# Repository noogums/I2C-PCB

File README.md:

i2c-sensor-logger:
  - A 2-layer PCB that logs temperature, humidity, and ambient light over I2C to CSV via USB serial and displays live readings on an SSD1306 OLED. 
    Built around the Raspberry Pi Pico W with TI HDC1080 and OPT3001 sensors.

Hardware:
  - Raspberry Pi Pico W
  - TI HDC1080 — temperature and humidity (±0.2°C, 14-bit)
  - TI OPT3001 — ambient light (23-bit dynamic range)
  - SSD1306 128x64 OLED display
  - MCP1700 3.3V LDO regulator
  - 2-layer FR4 PCB, manufactured by JLCPCB

Measurements: (updated once board comes in)
  - I2C bus waveforms — scope screenshot of SDA/SCL
  - Rise time measured vs calculated
  - Temperature accuracy vs reference thermometer
  - Power consumption on 3.3V rail
  - I2C frequency limit before communication fails

Schematic:

PCB:
  -Top:

  -Back:

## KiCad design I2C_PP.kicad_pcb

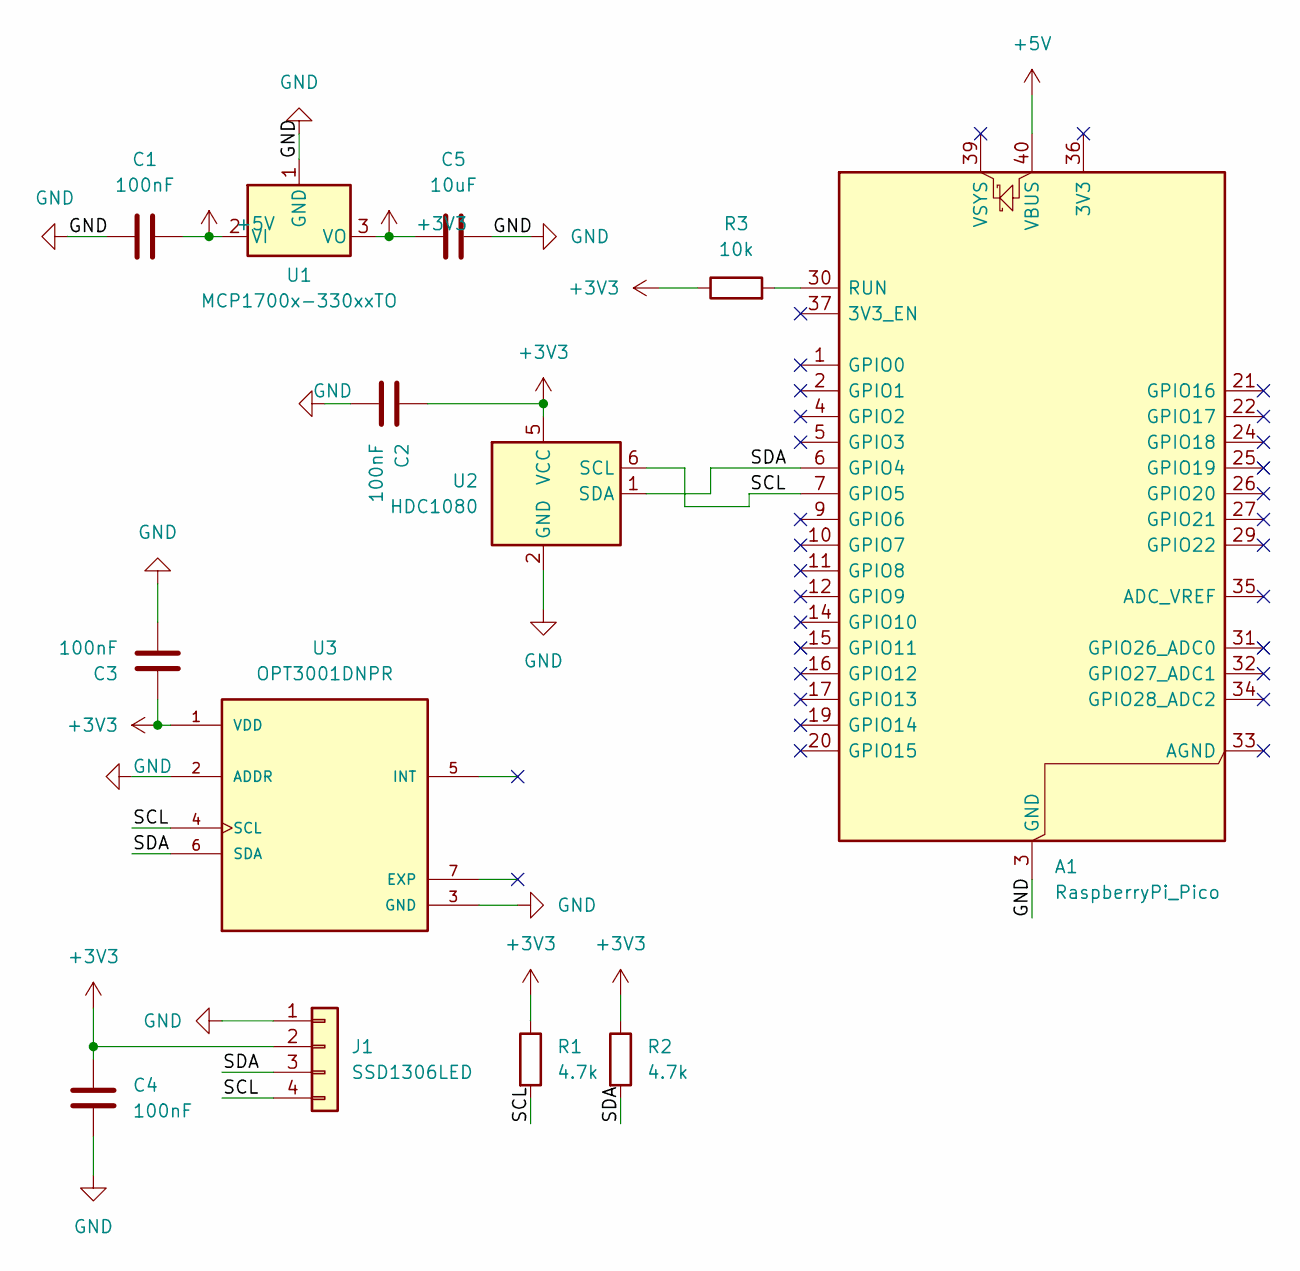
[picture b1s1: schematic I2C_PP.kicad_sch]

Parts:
A1: RaspberryPi_Pico; RaspberryPi_Pico_Common_Unspecified
C1, C2, C3, C4: 100nF; C_0603_1608Metric
C5: 10uF; C_0805_2012Metric
J1: SSD1306LED; PinHeader_1x04_P2.54mm_Vertical
R1, R2: 4.7k; R_0603_1608Metric
R3: 10k; R_0603_1608Metric
U1: MCP1700x-330xxTO; TO-92_Inline
U2: HDC1080; Texas_PWSON-N6
U3: OPT3001DNPR; SON65P200X200X65-7N

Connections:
+3V3: C2.1, C3.1, C4.1, C5.1, J1.2, R1.1, R2.1, R3.1, U1.3 (VO), U2.5 (VCC), U3.1 (VDD)
+5V: A1.40 (VBUS), C1.2, U1.2 (VI)
/SCL: A1.7 (GPIO5), J1.4, R1.2, U2.6 (SCL), U3.4 (SCL)
/SDA: A1.6 (GPIO4), J1.3, R2.2, U2.1 (SDA), U3.6 (SDA)
GND: A1.3 (GND), A1.8 (GND), A1.13 (GND), A1.18 (GND), A1.23 (GND), A1.28 (GND), A1.38 (GND), C1.1, C2.2, C3.2, C4.2, C5.2, J1.1, U1.1 (GND), U2.2 (GND), U3.2 (ADDR), U3.3 (GND)
unnamed: A1.30 (RUN), R3.2

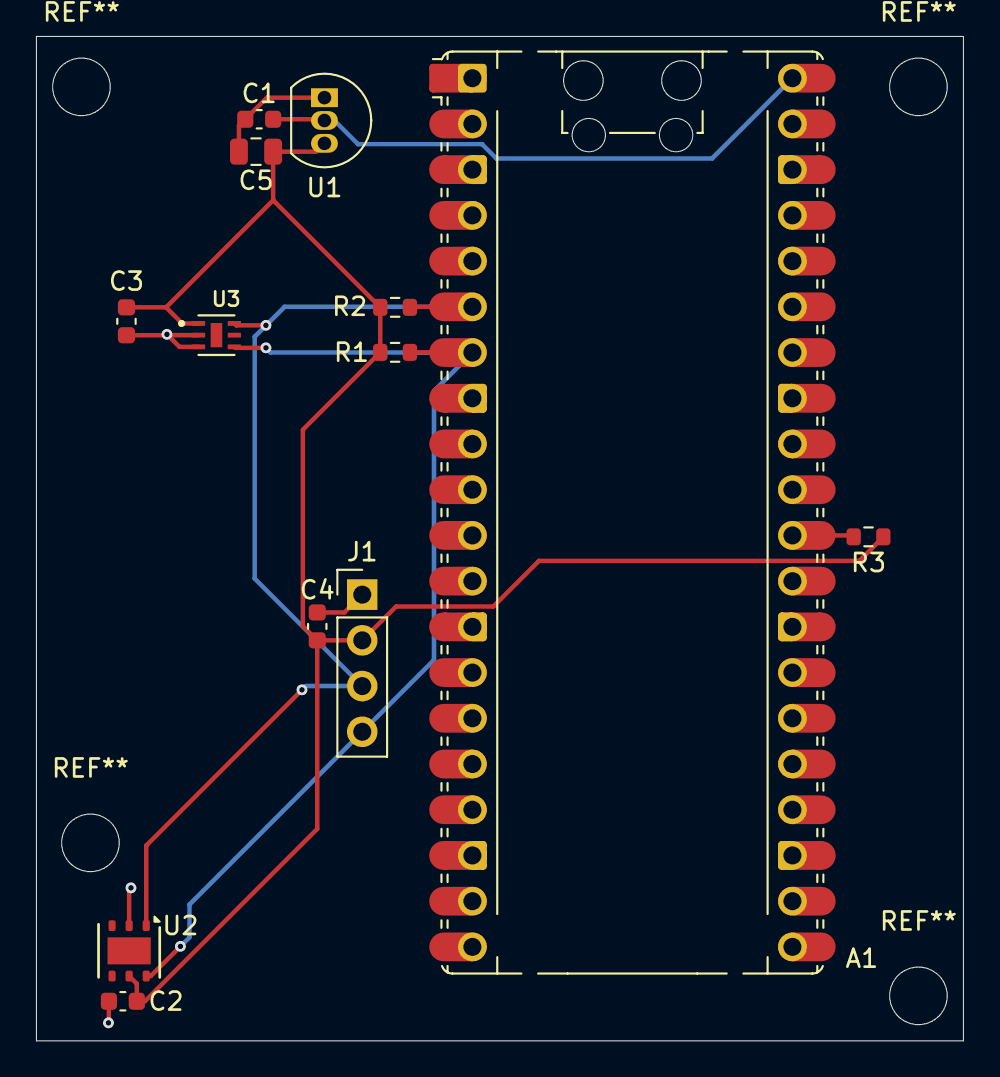
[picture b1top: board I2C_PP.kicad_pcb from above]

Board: 2 copper layers, 51.5 x 55.8 mm, 13 parts (0 on the bottom side), 6 nets.

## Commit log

2026-06-11 Add files via upload
    Photo of JLCPCB top view
